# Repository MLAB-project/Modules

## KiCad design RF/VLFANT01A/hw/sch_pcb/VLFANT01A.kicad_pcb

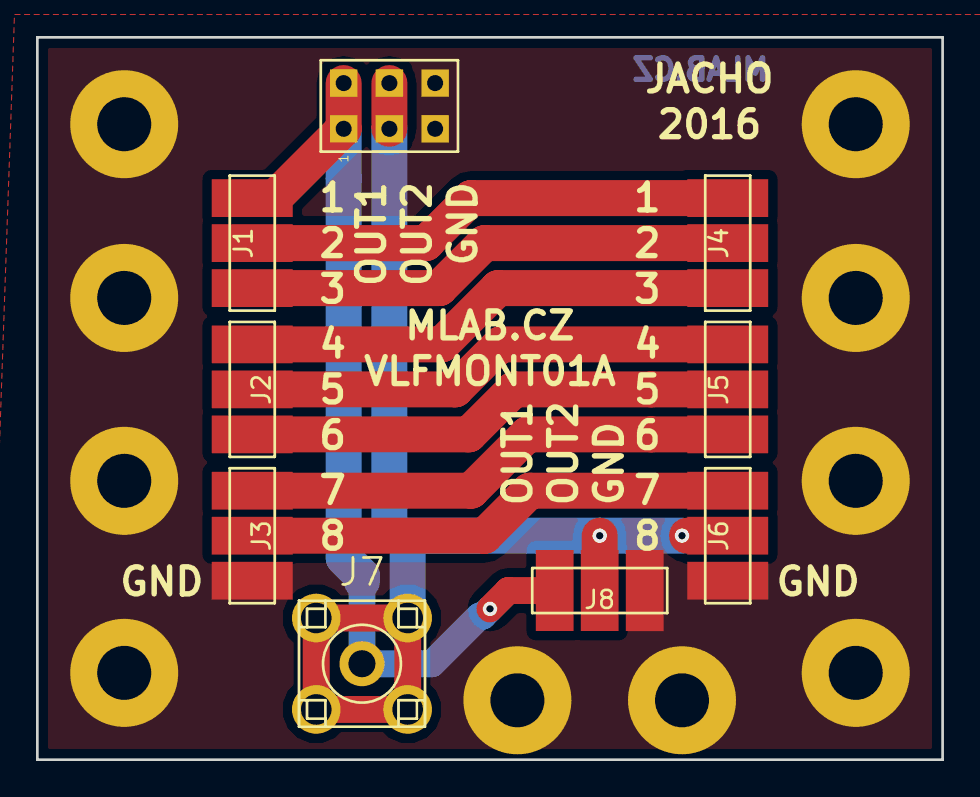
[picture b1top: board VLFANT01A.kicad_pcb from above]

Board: 2 copper layers, 50.3 x 40.1 mm, 19 parts (0 on the bottom side), 10 nets.

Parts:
J1, J2, J3, J4, J5, J6, J8: CONN_3; AVX_009175003001006
J7: SMA; SMA6251A13G50
J9: JUMP_3X2; Straight_2x03
M1, M2, M3, M4, M5, M6, M7, M8, M9, M10: HOLE; MountingHole_3mm

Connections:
/1: J1.2, J4.1
/2: J1.3, J4.2
/3: J2.3, J4.3
/4: J2.2, J5.1
/5: J2.1, J5.2
/6: J3.3, J5.3
/7: J3.2, J6.1
/OUT1: J1.1, J7.1, J8.1, J9.1, J9.2
/OUT2: J6.2, J7.2, J8.2, J9.3, J9.4
GND: J3.1, J6.3, J8.3, J9.5, J9.6, M1.1, M2.1, M3.1, M4.1, M5.1, M6.1, M7.1, M8.1, M9.1, M10.1

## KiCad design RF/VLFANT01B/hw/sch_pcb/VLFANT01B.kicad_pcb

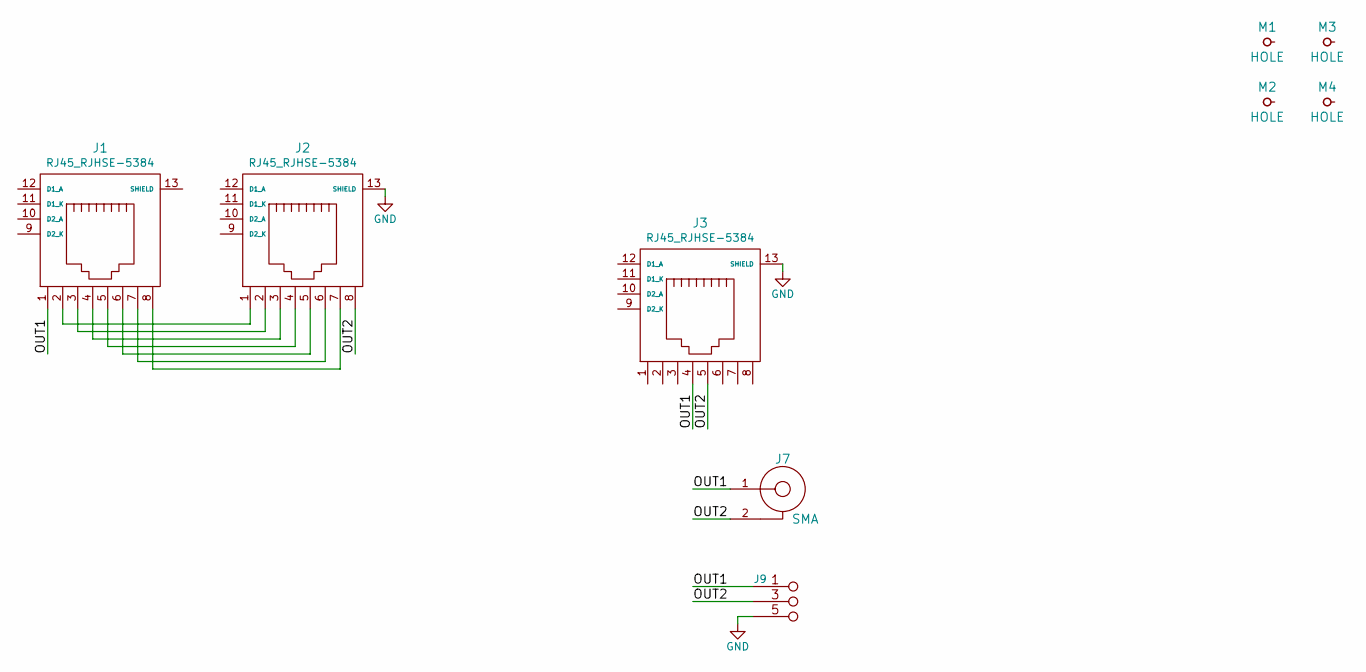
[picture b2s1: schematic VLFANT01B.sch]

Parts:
J1, J2, J3: RJ45_RJHSE-5384; RJHSE-5384(RJ45)
J7: SMA; SMA6251A13G50
J9: JUMP_3X2; Straight_2x03
M1, M2, M3, M4: HOLE; MountingHole_3mm

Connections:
/OUT1: J1.1, J3.4, J7.1, J9.1 (2), J9.2
/OUT2: J2.8, J3.5, J7.2, J9.3 (4), J9.4
GND: J2.13 (SHIELD), J3.13 (SHIELD), J9.5 (6), J9.6
unnamed: J1.2, J2.1
unnamed: J1.3, J2.2
unnamed: J1.4, J2.3
unnamed: J1.5, J2.4
unnamed: J1.6, J2.5
unnamed: J1.7, J2.6
unnamed: J1.8, J2.7

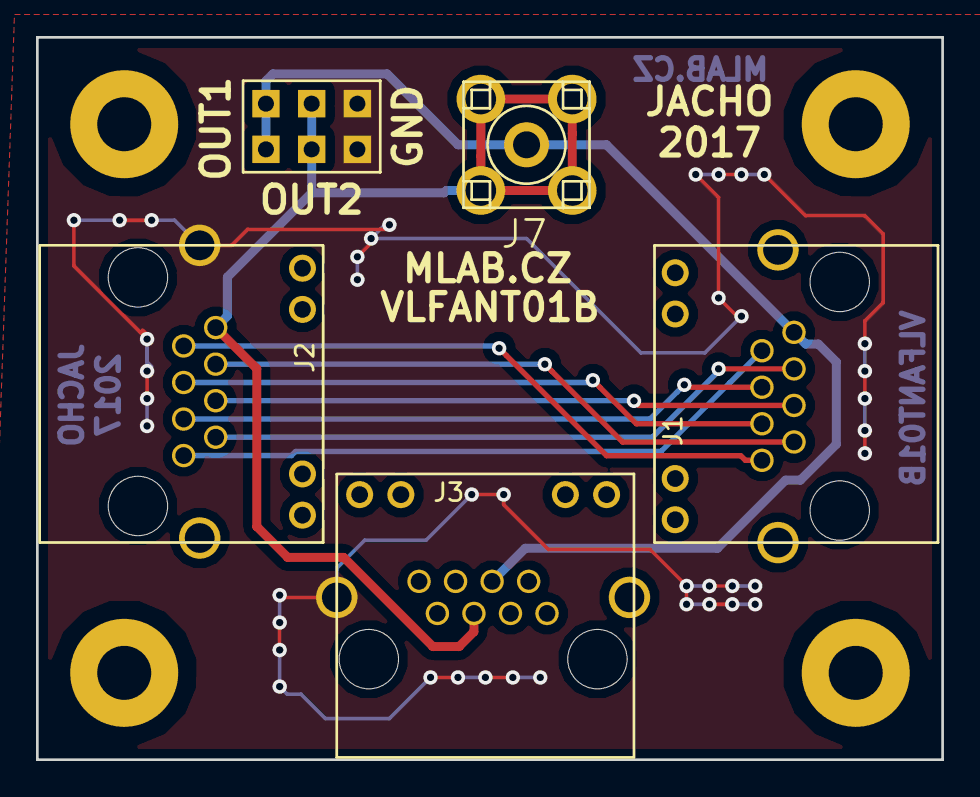
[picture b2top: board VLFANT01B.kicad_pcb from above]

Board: 2 copper layers, 50.3 x 40.1 mm, 9 parts (0 on the bottom side), 10 nets.

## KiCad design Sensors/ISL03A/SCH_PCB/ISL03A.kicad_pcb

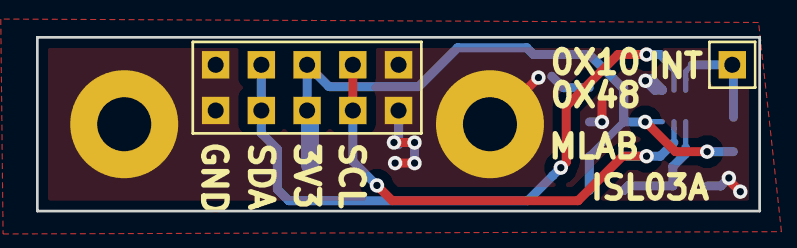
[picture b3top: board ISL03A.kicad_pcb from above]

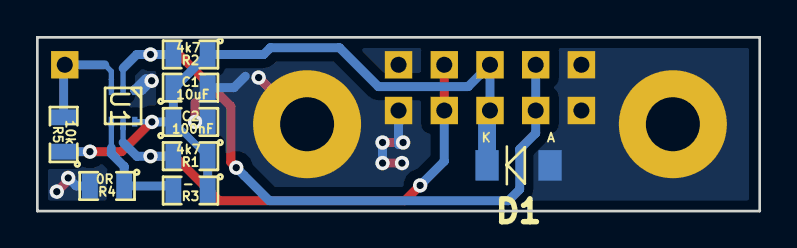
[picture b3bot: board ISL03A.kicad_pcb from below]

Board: 2 copper layers, 40.1 x 9.7 mm, 13 parts (9 on the bottom side), 6 nets.

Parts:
C1: 10uF; SMD-0805
C2: 100nF; SMD-0805
D1: BZV55C-3,6V; Diode-MiniMELF_Standard
J1: JUMP_5X2; Straight_2x05
J2: CONN1_1; Straight_1x01
M1, M2: HOLE; MountingHole_3mm
R1, R2: 4k7; SMD-0805
R3: -; SMD-0805
R4: 0R; SMD-0805
R5: 10k; SMD-0805
U1: VEML6030

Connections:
+3V3: C1.1, C2.1, D1.2, J1.5, J1.6, R1.1, R2.1, R3.1, R5.1, U1.6
/INT: J2.1, R5.2, U1.3
/SCL: J1.7, J1.8, R1.2, U1.5
/SDA: J1.3, J1.4, R2.2, U1.2
GND: C1.2, C2.2, D1.1, J1.1, J1.2, J1.9, J1.10, M1.1, M2.1, R4.2, U1.1
unnamed: R3.2, R4.1, U1.4

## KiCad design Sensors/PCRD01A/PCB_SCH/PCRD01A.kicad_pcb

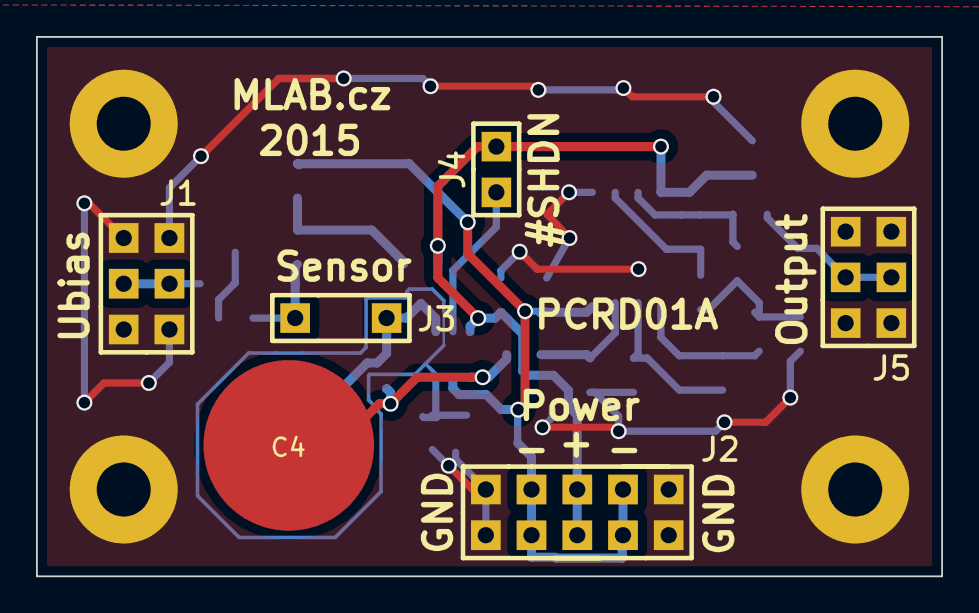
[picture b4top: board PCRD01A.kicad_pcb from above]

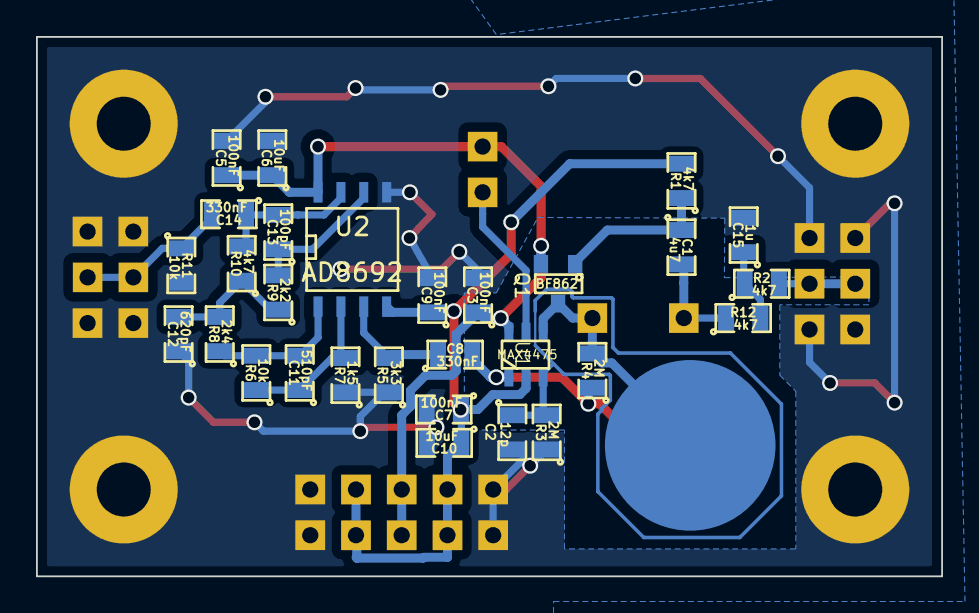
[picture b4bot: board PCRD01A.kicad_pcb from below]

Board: 2 copper layers, 50.3 x 30.0 mm, 39 parts (29 on the bottom side), 18 nets.

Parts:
C1: 4u7; SMD-0805
C2: 12p; SMD-0805
C3, C5, C7, C9: 100nF; SMD-0805
C4: 2pF; 2pF_PCB
C6, C10: 10uF; SMD-0805
C8, C14: 330nF; SMD-0805
C11: 510pF; SMD-0805
C12: 620pF; SMD-0805
C13: 100pF; SMD-0805
C15: 1u; SMD-0805
J1: JUMP_3X2; Pin_Header_Straight_2x03
J2: JUMP_5X2; Pin_Header_Straight_2x05
J3: CONN1_2; CONN_3_2
J4: CONN1_2; Pin_Header_Straight_1x02
J5: Out; Pin_Header_Straight_2x03
P1, P2, P3, P4: _; MountingHole_3mm
Q1: BF862; SOT-23
R1, R2, R10, R12: 4k7; SMD-0805
R3, R4: 2M; SMD-0805
R5: 3k3; SMD-0805
R6, R11: 10k; SMD-0805
R7: 1k5; SMD-0805
R8: 2k4; SMD-0805
R9: 2k2; SMD-0805
U1: MAX4475; SOT-23-6
U2: AD8692; SOIC-8-N

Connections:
/#SHDN: J4.1, U1.5
/+Ubias: J1.2, J1.5, R2.2
/A: C4.2, J3.2, Q1.3, R4.2, U1.4
/K: C1.2, J3.1, R12.1
GND: C2.2, C3.2, C5.2, C6.2, C7.2, C9.2, C10.2, C12.1, C15.2, J1.1, J1.3, J1.4, J1.6, J2.1, J2.5, J2.6, J2.10, J5.1, J5.3, J5.4, J5.6, P1.1, P2.1, P3.1, P4.1, R3.1, R5.1, R7.1, R11.2, U2.5
unnamed: C1.1, Q1.1, R1.1
unnamed: C2.1, R3.2, U1.3
unnamed: C4.1, C8.2, R4.1, U1.1
unnamed: C8.1, R5.2, U2.3
unnamed: C11.1, R6.1, R7.2, U2.2
unnamed: C11.2, R6.2, R8.1, U2.1
unnamed: C12.2, R8.2, R9.1, R10.1
unnamed: C13.1, R9.2, U2.6
unnamed: C13.2, C14.1, R10.2, U2.7
unnamed: C14.2, J5.2, J5.5, R11.1
unnamed: C15.1, R2.1, R12.2
V+: C3.1, C5.1, C6.1, J2.3, J2.8, J4.2, Q1.2, U1.6, U2.8
V-: C7.1, C9.1, C10.1, J2.2, J2.4, J2.7, J2.9, R1.2, U1.2, U2.4

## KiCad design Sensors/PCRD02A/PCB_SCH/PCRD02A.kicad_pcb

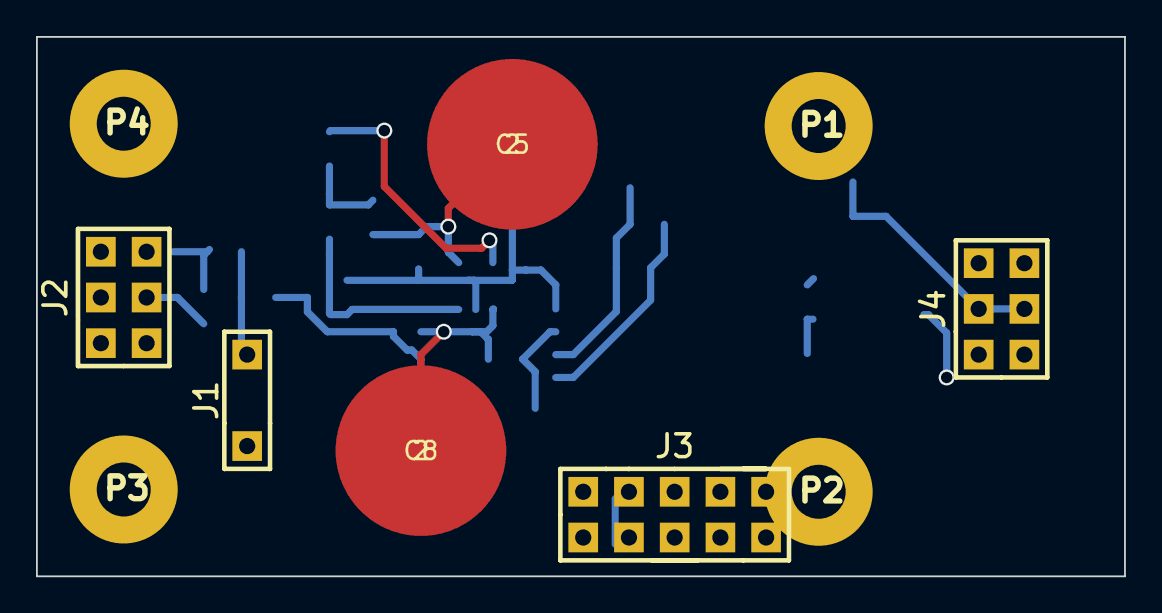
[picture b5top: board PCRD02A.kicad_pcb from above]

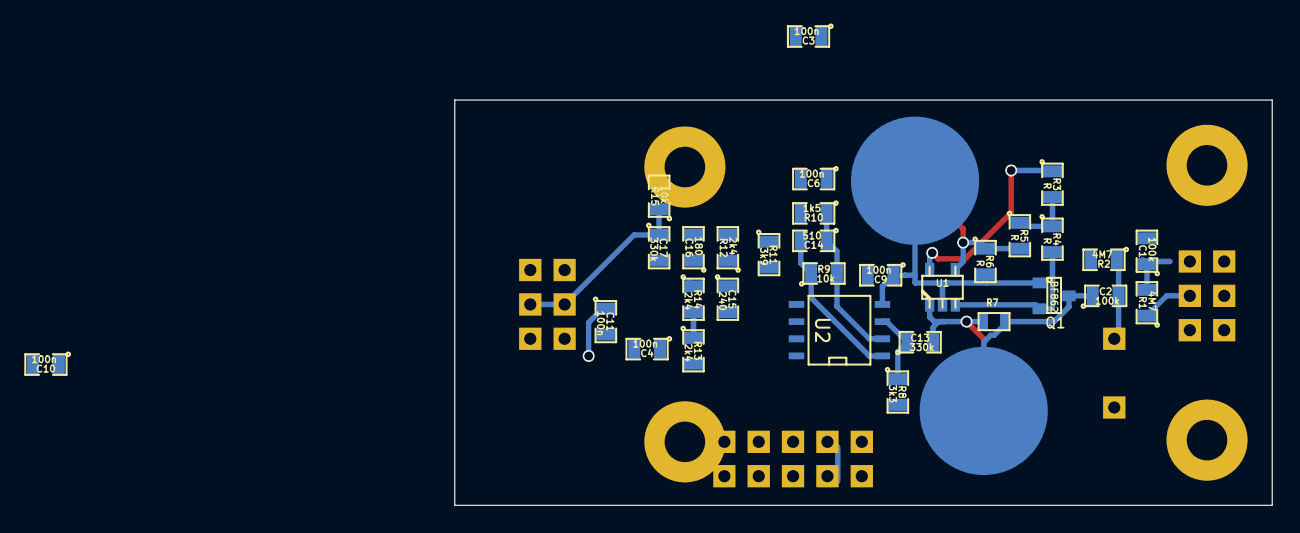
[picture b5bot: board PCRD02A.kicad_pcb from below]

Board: 2 copper layers, 60.4 x 30.0 mm, 41 parts (31 on the bottom side), 19 nets.

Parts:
C1, C2: 100k; SMD-0805
C3, C4, C6, C9, C10, C11: 100n; SMD-0805
C5, C8: 2; C2pF
C13, C17: 330k; SMD-0805
C14: 510; SMD-0805
C15: 240; SMD-0805
C16: 180; SMD-0805
J1: CONN1_2; CONN_3_2
J2: JUMP_3X2; Pin_Header_Straight_2x03
J3: JUMP_5X2; Pin_Header_Straight_2x05
J4: Out; Pin_Header_Straight_2x03
P1, P2, P3, P4: _; MountingHole_3mm
Q1: BF862; SOT-23
R1, R2: 4M7; SMD-0805
R3, R4, R5, R6: R; SMD-0805
R7: 2M; SMD-0603
R8: 3k3; SMD-0805
R9, R15: 10k; SMD-0805
R10: 1k5; SMD-0805
R11: 3k9; SMD-0805
R12, R13, R14: 2k4; SMD-0805
U1: AD8691; tsot-5
U2: AD8692; SOIC-8-N

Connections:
GND: C1.2, C3.2, C4.2, C6.2, C9.2, C10.2, C11.2, C15.2, J1.1, J2.1, J2.3, J2.4, J2.6, J3.1, J3.5, J3.6, J3.10, J4.1, J4.3, J4.4, J4.6, P1.1, P2.1, P3.1, P4.1, R8.2, R10.2, R13.2, R15.2
unnamed: C1.1, R1.2, R2.1
unnamed: C2.1, C8.2, Q1.3, R7.2
unnamed: C2.2, J1.2, R2.2
unnamed: C5.1, R5.2, R6.1, U1.4
unnamed: C13.1, R8.1, U2.3
unnamed: C8.1, C13.2, R7.1, U1.1
unnamed: C14.1, R9.2, R10.1, U2.2
unnamed: C14.2, R9.1, R11.2, U2.1
unnamed: C15.1, R12.1, U2.5
unnamed: C16.1, C17.2, R14.1, U2.7
unnamed: C16.2, R11.1, R12.2
unnamed: C17.1, J4.2, J4.5, R15.1
unnamed: J2.2, J2.5, R1.1
unnamed: Q1.2, R4.2, U1.3
unnamed: R3.2, R4.1, R5.1
unnamed: R13.1, R14.2, U2.6
V+: C3.1, C4.1, C6.1, J3.3, J3.8, R3.1, U1.5, U2.8
V-: C5.2, C9.1, C10.1, C11.1, J3.2, J3.4, J3.7, J3.9, Q1.1, R6.2, U1.2, U2.4

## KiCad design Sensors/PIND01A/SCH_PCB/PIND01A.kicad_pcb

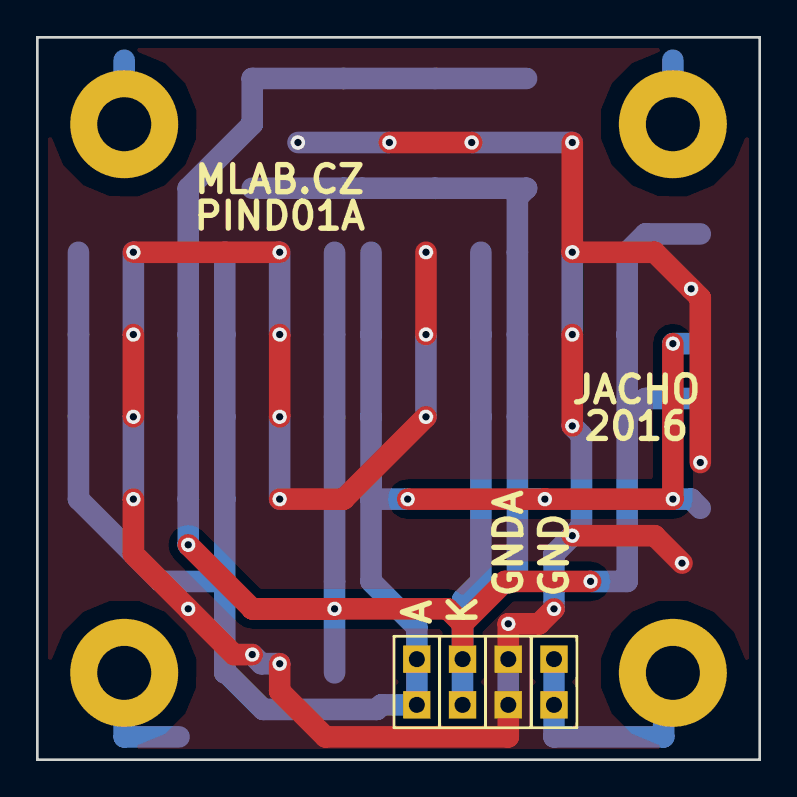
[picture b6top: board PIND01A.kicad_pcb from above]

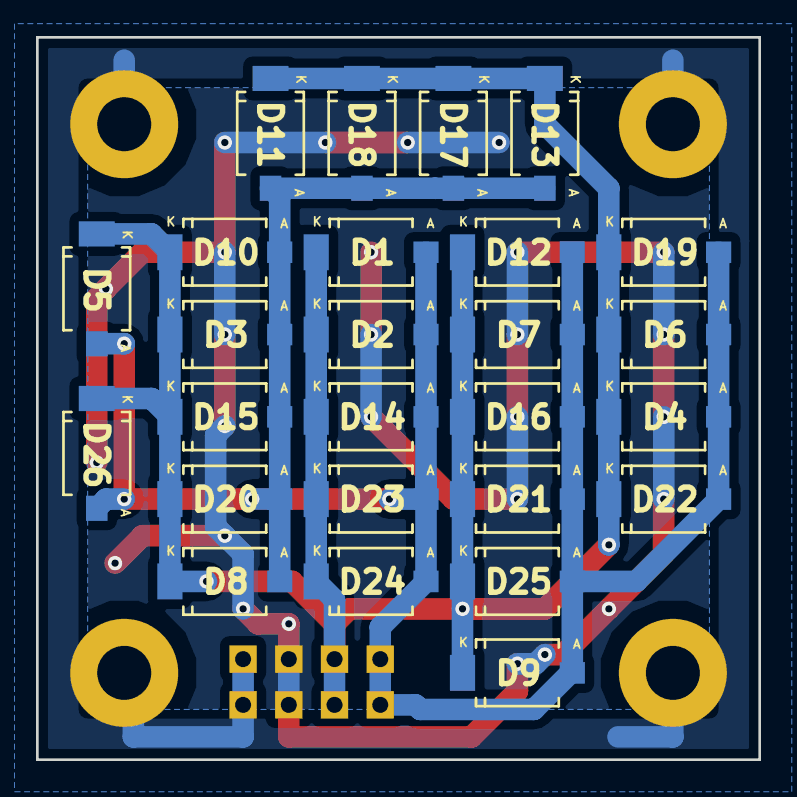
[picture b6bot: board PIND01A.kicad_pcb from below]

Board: 2 copper layers, 40.1 x 40.1 mm, 34 parts (26 on the bottom side), 4 nets.

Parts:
D1, D2, D3, D4, D5, D6, D7, D8, D9, D10, D11, D12, D13, D14, D15, D16, D17, D18, D19, D20, D21, D22, D23, D24, D25, D26: BPW34S; DIL
J1, J2, J3, J4: JUMP_2x1; Straight_2x01
M1, M2, M3, M4: HOLE; MountingHole_3mm

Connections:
/A: D1.2, D2.2, D3.2, D4.2, D5.2, D6.2, D7.2, D8.2, D9.2, D10.2, D11.2, D12.2, D13.2, D14.2, D15.2, D16.2, D17.2, D18.2, D19.2, D20.2, D21.2, D22.2, D23.2, D24.2, D25.2, D26.2, J1.1, J1.2
/K: D1.1, D2.1, D3.1, D4.1, D5.1, D6.1, D7.1, D8.1, D9.1, D10.1, D11.1, D12.1, D13.1, D14.1, D15.1, D16.1, D17.1, D18.1, D19.1, D20.1, D21.1, D22.1, D23.1, D24.1, D25.1, D26.1, J2.1, J2.2
GND: J4.1, J4.2, M1.1, M2.1, M3.1, M4.1
GNDA: J3.1, J3.2

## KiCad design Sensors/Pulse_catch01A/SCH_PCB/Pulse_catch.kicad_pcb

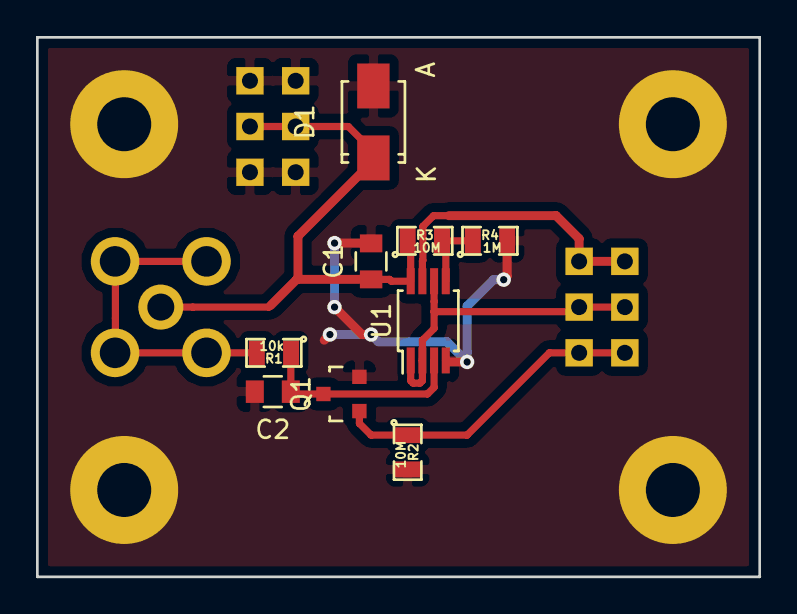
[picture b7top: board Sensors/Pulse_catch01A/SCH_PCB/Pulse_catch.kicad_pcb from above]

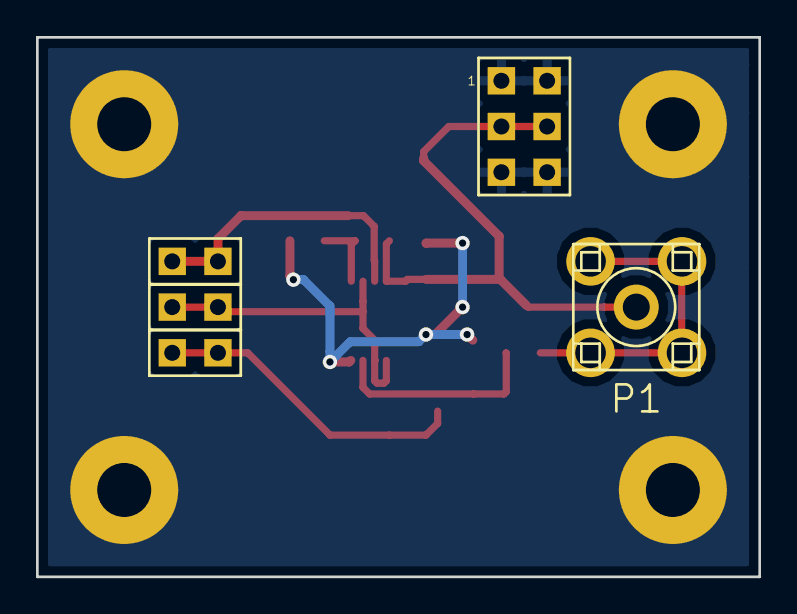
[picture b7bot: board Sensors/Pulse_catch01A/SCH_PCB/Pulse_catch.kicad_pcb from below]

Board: 2 copper layers, 40.1 x 30.0 mm, 18 parts (5 on the bottom side), 8 nets.

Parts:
C1, C2: 100nF; C_0805
D1: D_Schottky; SMA_Standard
J1: HEADER_2x03_PARALLEL; Straight_2x03
J2: INTENSITY; Straight_2x01
J3: RESET; Straight_2x01
J4: INT_OUT; Straight_2x01
M1, M2, M3, M4: HOLE; MountingHole_3mm
P1: SMA; SMA6251A13G50
Q1: 2N7002; SOT-23
R1: 10k; SMD-0805
R2, R3: 10M; SMD-0805
R4: 1M; SMD-0805
U1: MCP6002; MSOP-8_3x3mm_Pitch0.65mm

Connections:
GNDA: C1.2, C2.2, D1.2, J1.1, J1.2, J1.5, J1.6, M1.1, M2.1, M3.1, M4.1, Q1.2, R2.2, R4.2, U1.4
unnamed: C2.1, Q1.3, R1.1, U1.3
unnamed: J2.1, J2.2, U1.1, U1.2, U1.6
unnamed: J3.1, J3.2, Q1.1, R2.1
unnamed: J4.1, J4.2, U1.7
unnamed: P1.2, R1.2
unnamed: R3.2, R4.1, U1.5
VDD: C1.1, D1.1, J1.3, J1.4, P1.1, R3.1, U1.8

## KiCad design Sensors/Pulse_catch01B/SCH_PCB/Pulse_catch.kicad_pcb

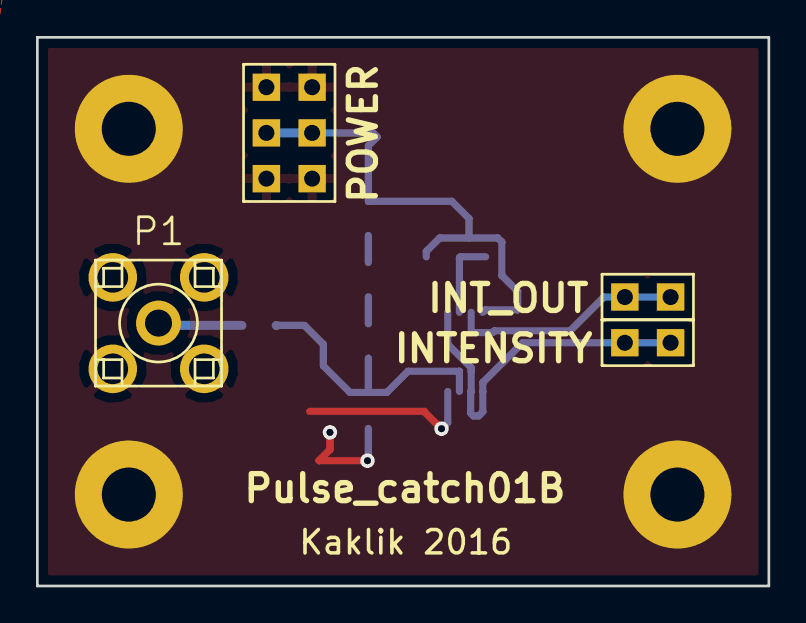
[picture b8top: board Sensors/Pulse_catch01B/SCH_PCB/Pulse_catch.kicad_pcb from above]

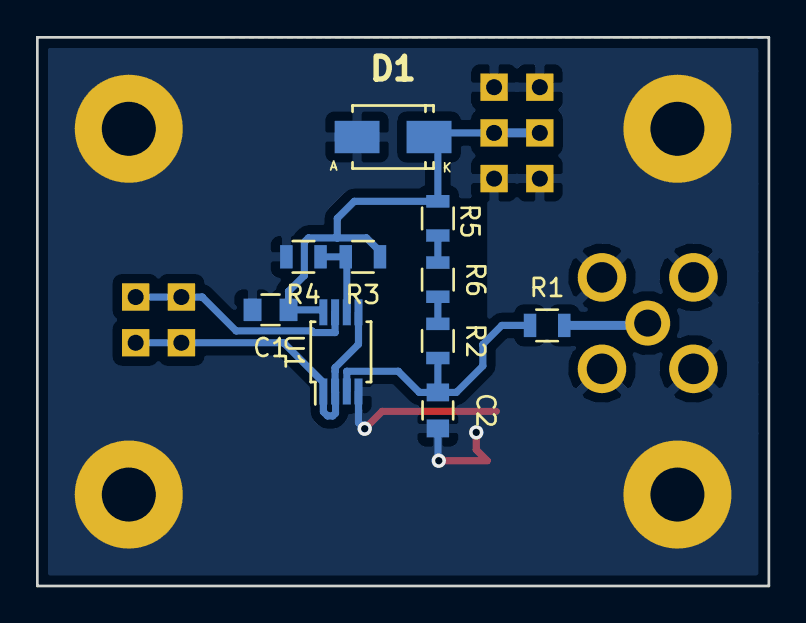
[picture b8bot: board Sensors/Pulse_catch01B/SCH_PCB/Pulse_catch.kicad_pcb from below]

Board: 2 copper layers, 40.6 x 30.5 mm, 18 parts (10 on the bottom side), 9 nets.

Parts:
C1, C2: 100nF; C_0805
D1: D_Schottky; Diode-SMA_Standard
J1: HEADER_2x03_PARALLEL; Straight_2x03
J2: INTENSITY; Straight_1x02
J3: INT_OUT; Straight_1x02
M1, M2, M3, M4: HOLE; MountingHole_3mm
P1: SMA; SMA6251A13G50
R1: 10k; R_0805
R2, R4, R5, R6: 10M; R_0805
R3: 1M; R_0805
U1: MCP6002; MSOP-8_3x3mm_Pitch0.65mm

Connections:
GNDA: C1.2, C2.2, D1.2, J1.1, J1.2, J1.5, J1.6, M1.1, M2.1, M3.1, M4.1, P1.2, R4.2, U1.4
unnamed: C2.1, R1.1, R2.2, U1.3
unnamed: J2.1, J2.2, U1.1, U1.2, U1.5
unnamed: J3.1, J3.2, U1.7
unnamed: P1.1, R1.2
unnamed: R2.1, R6.2
unnamed: R3.2, R4.1, U1.6
unnamed: R5.2, R6.1
VDD: C1.1, D1.1, J1.3, J1.4, R3.1, R5.1, U1.8
